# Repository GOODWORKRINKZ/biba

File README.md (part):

# BiBa

BiBa — это колесная робот-платформа с управлением по ExpressLRS/CRSF, телеметрией от Daly 6S BMS по BLE или USB-UART, двухканальными драйверами BTS7960 и звуковой индикацией через моторы. Платформа поддерживает три композиции железа — от чисто-Pi-варианта до связки одноплатник + STM32F103, поэтому репозиторий организован как hub: общие компоненты живут рядом, а сборки разводятся по подкаталогам.

## Архитектура

BiBa поддерживает три композиции железа. Где есть STM32 — именно он принимает CRSF и держит failsafe; одноплатник, если присутствует, работает как high-level brain поверх SPI-канала к STM32.

| Композиция | SBC (Raspberry Pi) | MCU add-on | Кто слушает CRSF | Compose / прошивка |
| --- | --- | --- | --- | --- |
| **A. Pi-only** (текущий продакшен) | да | нет | Pi (`/dev/ttyS0`) | [`docker/legacy-pi/docker-compose.yml`](docker/legacy-pi/docker-compose.yml) |
| **B. STM32-only** | нет | STM32F103 | STM32 | env `standalone` в [`firmware/`](firmware/) |
| **C. Pi + STM32** | да | STM32F103 | STM32 (Pi видит каналы через SPI-телеметрию) | env `companion` в [`firmware/`](firmware/) + ROS2-стек в `docker/ros2/` (в разработке) |
| **D. RP2040-only** (в разработке, ветка `rp2040-port`) | нет | RP2040 | RP2040 | env `rp2040_dc_bts7960_pwm_standalone` в [`firmware/`](firmware/) |

Канонический разбор композиций, их обязанности и failsafe-уровни — в [docs/system_architecture.md](docs/system_architecture.md). STM32-сторона детально описана в [docs/stm32_architecture.md](docs/stm32_architecture.md), будущий ROS2-стек композиции C — в [docs/ros2_stack.md](docs/ros2_stack.md). Общий design-doc и план редизайна — [docs/plans/2026-04-28-sbc-architecture-redesign-design.md](docs/plans/2026-04-28-sbc-architecture-redesign-design.md).

## Состав железа

- Raspberry Pi Zero 2W
- ELRS-приемник с подключением по UART/CRSF
- Daly BMS по BLE или с USB-UART адаптером
- 6S аккумулятор с телеметрией BMS
- Два драйвера BTS7960 для левого и правого моторов
- ADS1115 для current sense и телеметрии токов колёс (опционально)

## Распиновка

| Назначение | BCM | Физический пин |
| --- | --- | --- |
| ELRS TX | 14 | 8 |
| ELRS RX | 15 | 10 |
| I2C SDA (ADS1115, опционально) | 2 | 3 |
| I2C SCL (ADS1115, опционально) | 3 | 5 |
| Left BTS7960 RPWM | 12 | 32 |
| Left BTS7960 LPWM | 18 | 12 |
| Left BTS7960 REN | 23 | 16 |
| Left BTS7960 LEN | 24 | 18 |
| Right BTS7960 RPWM | 19 | 35 |
| Right BTS7960 LPWM | 13 | 33 |
| Right BTS7960 REN | 20 | 38 |
| Right BTS7960 LEN | 21 | 40 |
| GND драйвера | - | 14 |

Распиновка и таблица выше актуальны для композиции A (Pi-only). Для композиций B/C wiring между Pi, STM32 и силовой частью описан в [docs/wiring.md](docs/wiring.md) и [docs/stm32_architecture.md](docs/stm32_architecture.md).

Подробное описание подключения находится в [docs/wiring.md](docs/wiring.md).

Опциональная прошивка для STM32F103 ("Blue Pill") add-on, который умеет работать либо самостоятельно, либо SPI-slave-ом к Pi, живёт в [`firmware/`](firmware/). Архитектура описана в [docs/stm32_architecture.md](docs/stm32_architecture.md).

Текущий двухмоторный runtime на Pi Zero 2W должен быть запущен с `BTS7960_PWM_MODE=SOFTWARE`, потому что распиновка `12/18` и `19/13` делит общие hardware-PWM каналы. Это уже совпадает и с кодовым default в `config.py`, и с compose-default для развёрнутого робота.

## Структура репозитория

- `biba-controller/` — Python-контроллер для CRSF, моторов, моторного audio/voice runtime и телеметрии BMS (композиции A и C)
- `biba-controller/stm32_link/` — опциональный SPI-клиент к STM32F103 add-on (`STM32_LINK_ENABLED=1`, композиция C)
- `firmware/` — PlatformIO-проект прошивки (STM32F103C8T6 и RP2040): env'ы `standalone` для композиции B, `companion` для композиции C, `rp2040_dc_bts7960_pwm_standalone` для композиции D (ветка `rp2040-port`), `native_test` для host-side Unity-тестов
- `docker/` — каталог compose-стеков, разнесённых по композициям:
  - `docker/legacy-pi/` — текущий продакшен-стек композиции A
  - `docker/ros2/` — будущий ROS2-стек композиции C (в разработке)
  - `docker/base/` — общие базовые образы (в разработке)
- `lua/SCRIPTS/TELEMETRY/biba.lua` — экран телеметрии EdgeTX для оператора
- `.github/workflows/` — global builder workflows для Ruff, pytest, shellcheck и сборки arm64 Docker-образа в GHCR
- `scripts/setup/` — bringup-скрипты для Raspberry Pi (Docker, Compose, systemd-автозапуск)
- `scripts/biba_aliases.sh` — robot-side operational aliases, включая `bbupdate` для штатного обновления
- `scripts/diagnostics.sh` — диагностика хоста и контейнера
- `scripts/voice_prep.py` — офлайн-подготовка русскоязычных voice assets и явный promote в production voice каталог
- `voice-src/phrases.yml` — канонический набор русских фраз по событиям
- `voice-work/` — staging-каталог для сгенерированных кандидатов перед promote в production voice каталог
- `docs/deployment.md` — руководство по развёртыванию по композициям
- `docs/system_architecture.md` — канонический обзор всех трёх композиций
- `firmware/docs/openipc_wfb.md` — приём FPV-видео с OpenIPC-камеры по радио (RTL8812AU + wfb-ng)
- `.agents/skills/` — вендорный каталог skills

## Quick-start по композициям

- **Композиция A (Pi-only).** Сегодняшний bringup-скрипт и compose-стек. Полный гайд: [docs/deployment.md](docs/deployment.md#композиция-a-pi-only).
- **Композиция B (STM32-only).** Без одноплатника. Сборка и заливка прошивки описаны в [firmware/README.md](firmware/README.md) и [docs/stm32_architecture.md](docs/stm32_architecture.md).
- **Композиция C (Pi + STM32).** В разработке. Проектная картина — в [design-doc](docs/plans/2026-04-28-sbc-architecture-redesign-design.md) и [docs/ros2_stack.md](docs/ros2_stack.md).

Дальше по тексту разделы про подготовку Pi, env-переменные, settings UI и motor trim относятся к композиции A.

## Подготовка Raspberry Pi (композиция A)

1. Включите UART на Raspberry Pi.
2. Освободите основной UART от Bluetooth, добавив в конфигурацию:

   ```ini
   enable_uart=1
   dtoverlay=disable-bt
   ```

3. Перезагрузите Raspberry Pi.
4. Настройте Daly BMS по BLE или подключите USB-UART адаптер, если используете UART-вариант.
5. Если используете ADS1115 для current sense, включите I2C и проверьте наличие `/dev/i2c-1`.

Вместо ручной установки Docker/Compose можно использовать bringup-скрипт:

```bash
curl -fsSL https://raw.githubusercontent.com/GOODWORKRINKZ/biba/main/scripts/setup/setup_node.sh | bash
```

Скрипт:

- ставит Docker и Docker Compose plugin
- ставит базовые системные утилиты
- клонирует или обновляет репозиторий в `~/biba`
- настраивает алиасы для управления стеком
- создает `systemd` unit для автозапуска `docker compose`

## Запуск (композиция A)

Компоновка стека лежит в [`docker/legacy-pi/docker-compose.yml`](docker/legacy-pi/docker-compose.yml). На роботе все стандартные действия выполняются через `bb*`-aliases из [`scripts/biba_aliases.sh`](scripts/biba_aliases.sh) (`bbupdate`, `bbstart`, `bbstop`, `bblogs`, `bbpull`).

Если удобно работать без алиасов — указывайте compose-файл явно:

```bash
docker compose -f docker/legacy-pi/docker-compose.yml pull
docker compose -f docker/legacy-pi/docker-compose.yml up -d
```

Локальная сборка:

```bash
docker compose -f docker/legacy-pi/docker-compose.yml build
docker compose -f docker/legacy-pi/docker-compose.yml up -d
```

Путь к compose-файлу можно переопределить переменной `BIBA_COMPOSE_FILE` для скриптов и алиасов.

Контейнер запускает `pigpiod`, слушает ELRS CRSF кадры на `/dev/ttyS0`, управляет моторами, опрашивает Daly BMS по BLE или на `/dev/ttyUSB0` и отправляет батарейную телеметрию обратно на передатчик.

Docker-образ собирается под `linux/arm64`, чтобы совпадать с Raspberry Pi Zero 2W. Для этого `pigpiod` собирается внутри образа из upstream `pigpio`, так как готовый пакет `pigpio` отсутствует в Debian bookworm arm64.

## Конфигурация и переменные окружения (композиция A)

Все env-переменные ниже применяются к compose-стеку композиции A в [`docker/legacy-pi/docker-compose.yml`](docker/legacy-pi/docker-compose.yml). Тип драйвера и распиновку можно переопределить через них:

- `MOTOR_DRIVER_TYPE=BTS7960|PWM_DIR`
- `BTS7960_PWM_MODE=HARDWARE|SOFTWARE` — для Pi Zero 2W с текущей двухмоторной проводкой нужен `SOFTWARE`
- `PWM_FREQUENCY_HZ=20000` — частота software PWM; актуально только при `BTS7960_PWM_MODE=SOFTWARE`
- `LEFT_MOTOR_RPWM=12`
- `LEFT_MOTOR_LPWM=18`
- `LEFT_MOTOR_REN=23`
- `LEFT_MOTOR_LEN=24`
- `LEFT_MOTOR_ENABLED=1` — отключить левый мотор целиком (для отладки)
- `RIGHT_MOTOR_RPWM=19`
- `RIGHT_MOTOR_LPWM=13`
- `RIGHT_MOTOR_REN=20`
- `RIGHT_MOTOR_LEN=21`
- `RIGHT_MOTOR_ENABLED=1` — отключить правый мотор целиком (для отладки)
- `MOTOR1_INVERTED=0|1`
- `MOTOR2_INVERTED=0|1`
- `CRSF_BAUD=420000` — скорость UART для CRSF-приёмника (менять не нужно для стандартного ELRS)
- `ARM_THRESHOLD=0.3` — нормализованный порог CH_ARM для арминга
- `THROTTLE_FILTER_MODE=NONE|KALMAN` — фильтрация газа до wheel-mix; `NONE` по умолчанию, `KALMAN` сглаживает выбросы канала
- `THROTTLE_KALMAN_PROCESS_NOISE=0.02` — насколько быстро фильтр принимает изменения реального setpoint
- `THROTTLE_KALMAN_MEASUREMENT_NOISE=0.5` — насколько сильно фильтр подавляет шум и ложные выбросы канала
- `CH_SPEED_MODE=5` — `CH6` на передатчике; трёхпозиционный селектор скоростного режима для controller-side scaling газа и руля
- `CH_DRIVE_MODE=6` — `CH7` на передатчике; селектор режимов движения: `manual` и `stabilized`
- `DRIVE_MODE_LOW_THRESHOLD=-0.3`, `DRIVE_MODE_HIGH_THRESHOLD=0.3` — пороги переключения drive mode аналогично speed mode
- `SPEED_MODE_LOW_THRESHOLD=-0.3` — нижний порог селектора в нормализованном диапазоне `-1..1`; ниже этого значения включается режим `1`
- `SPEED_MODE_HIGH_THRESHOLD=0.3` — верхний порог селектора в нормализованном диапазоне `-1..1`; выше этого значения включается режим `3`
- `SPEED_MODE_SLOW_SCALE=0.3333333333333333` — коэффициент для режима `1`
- `SPEED_MODE_MEDIUM_SCALE=0.6666666666666666` — коэффициент для режима `2`
- `SPEED_MODE_FAST_SCALE=1.0` — коэффициент для режима `3`
- `IMU_ENABLED=0|1` — включает autodetect IMU backend на I2C: BMI160/BMI166 или ST LSM6DS3-class
- `IMU_I2C_BUS=1`, `IMU_I2C_ADDRESS=104`, `IMU_EXPECTED_CHIP_ID=209` — параметры подключения IMU; на текущем роботе ST-модуль отвечает по `0x6A`, так что для него нужен `IMU_I2C_ADDRESS=106`
- `IMU_SAMPLE_RATE_HZ=100.0`, `IMU_STALE_TIMEOUT_S=0.2`, `IMU_GYRO_BIAS_CALIBRATION_S=1.0`, `IMU_GYRO_Z_SIGN=1.0` — частота чтения, timeout свежести, длительность bias-калибровки и знак yaw-оси
- `DRIVE_MODE_STEERING_DEADBAND=0.05`, `DRIVE_MODE_STEERING_LIMIT=1.0`, `DRIVE_MODE_YAW_RATE_MAX_DPS=90.0` — базовые ограничения assist-контура
- `DRIVE_MODE_YAW_RATE_KP/KI/KD` — tuning-параметры yaw-rate контура stabilized режима
- `DRIVE_MODE_YAW_RATE_DEADBAND_DPS`, `DRIVE_MODE_YAW_RATE_FILTER_HZ` — подавление мелкого gyro noise и сглаживание yaw-rate feedback
- `DRIVE_MODE_STABILIZATION_MIN_THROTTLE`, `DRIVE_MODE_NEUTRAL_STABILIZATION_STEERING_LIMIT`, `DRIVE_MODE_NEUTRAL_STABILIZATION_MAX_THROTTLE` — low-speed ограничения stabilized режима
- `PID_TUNING_SETTINGS_PATH=/data/pid-tuning.json` — persistent JSON с последними field-tuning значениями stabilized режима
- `LOW_CELL_VOLTAGE=3.5` — порог низкого напряжения ячейки для предупреждения `LOW` на Lua-экране
- `LOW_PACK_VOLTAGE=21.0` — порог низкого напряжения пакета (резервный, если ячейки не доступны)
- `BMS_BLE_ADDRESS=` — MAC-адрес BLE BMS (пустая строка = авто-поиск)
- `BMS_BLE_TIMEOUT_S=1.5` — таймаут BLE-операций
- `BMS_BLE_SERVICE_UUID`, `BMS_BLE_WRITE_UUID`, `BMS_BLE_NOTIFY_UUID` — UUID BLE-сервиса Daly (менять не нужно для стандартного Daly)
- `BMS_TELEMETRY_TRACE_ENABLED=0|1` — включает точные controller-side trace-логи на этапах consume/send для battery telemetry
- `BEACON_ENABLED=1` — включён по умолчанию; `0` отключает маяк совсем
- `BEACON_DELAY_S=300`
- `CH_BEACON=7` — `CH8` на передатчике; ручное включение маяка
- `CH_MUTE=9` — `CH10` на передатчике по умолчанию; канал мьюта обычных звуков, если нужен отдельный mute switch
- `CH_TRIM=8` — `CH9` на передатчике; в trim-mode используется как live-источник подстройки межколёсного баланса
- `MOTOR_TRIM_MAX_EFFECT=0.30` — максимальная коррекция, применяемая к одной стороне от полного хода `CH9`
- `MOTOR_TRIM_CONFIRM_HOLD_S=5.0` — сколько секунд держать trim-жест для входа и подтверждения
- `MOTOR_TRIM_SETTINGS_PATH=/data/motor-trim.json` — файл сохранённого trim на persistent Docker volume
- `ENABLE_RC_MELODIES=0|1` — включает выбор BLHeli-мелодий с передатчика
- `CH_MELODY=8` — канал выбора мелодии, если `ENABLE_RC_MELODIES=1`
- `STARTUP_MELODY=biba_signature` — стартовая BLHeli-мелодия при включённом melody-runtime
- `SOUND_MODE=SPECTRAL_VOICE|VOICE|SYNTH` — режим звуковой индикации: `SPECTRAL_VOICE` (по умолчанию) использует build-time spectral cache, `VOICE` — raw WAV, `SYNTH` — только BLHeli-мелодии без голоса
- `VOICE_SELECTION_MODE=ROUND_ROBIN|RANDOM` — порядок воспроизведения WAV при наличии нескольких вариантов на событие
- `MOTOR_TEST_API_ENABLED=1` — включён по умолчанию; `0` отключает встроенный HTTP settings UI контроллера
- `MOTOR_TEST_API_HOST=0.0.0.0` — bind host для settings UI
- `MOTOR_TEST_API_PORT=8765` — bind port для settings UI
- `RAMP_ACCEL_RATE=2.0` — скорость разгона мотора (единиц/сек, 0→100% за 0.5с)
- `RAMP_DECEL_RATE=2.0` — скорость отпускания/торможения (единиц/сек, 100%→0 за 0.5с)
- `RAMP_REVERSE_DECEL_RATE=0.5` — скорость подхода к нулю перед сменой направления; меньше значение = мягче переход в реверс
- `RAMP_ZERO_HOLD_S=0.15` — пауза на нуле (секунды) после торможения перед реверсом; даёт мотору физически остановиться и убирает «гавканье» BTS7960
- `MOTOR_DEADBAND=0.05` — мёртвая зона стика (меньше порога → мотор стоит)

Если нужно включить current sense через ADS1115, дополнительно задайте:

- `MOTOR_CURRENT_SENSE_ENABLED=1`
- `MOTOR_CURRENT_LIMITING_ENABLED=0|1` — включает software throttle back при превышении тока
- `MOTOR_CURRENT_SENSE_I2C_ADDRESS=72` (0x48 — стандартный адрес ADS1115)
- `MOTOR_CURRENT_SENSE_SAMPLE_RATE_HZ=32.0` — частота опроса ADS1115
- `MOTOR_CURRENT_SENSE_GAIN=1` — коэффициент усиления ADS1115 (1, 2, 4, 8, 16)
- `LEFT_MOTOR_CURRENT_SENSE_FORWARD_CHANNEL=2`, `LEFT_MOTOR_CURRENT_SENSE_REVERSE_CHANNEL=3`
- `RIGHT_MOTOR_CURRENT_SENSE_FORWARD_CHANNEL=0`, `RIGHT_MOTOR_CURRENT_SENSE_REVERSE_CHANNEL=1`
- `LEFT_MOTOR_CURRENT_SENSE_ZERO_OFFSET_V=0.0`, `RIGHT_MOTOR_CURRENT_SENSE_ZERO_OFFSET_V=0.0` — нулевые смещения для калибровки
- `LEFT_MOTOR_CURRENT_SENSE_AMPS_PER_VOLT=1.0`, `RIGHT_MOTOR_CURRENT_SENSE_AMPS_PER_VOLT=1.0` — коэффициент перевода напряжения в амперы
- `LEFT_MOTOR_MAX_CURRENT_A=18.0`, `RIGHT_MOTOR_MAX_CURRENT_A=18.0` — пороги ограничения тока
- `LEFT_MOTOR_MAX_POWER_W=180.0`, `RIGHT_MOTOR_MAX_POWER_W=180.0` — пороги ограничения мощности
- `MOTOR_LIMIT_FALLBACK_VOLTAGE=24.0` — напряжение пакета для расчёта мощности при отсутствии BMS данных

Для калибровочных заездов доступен отдельный trace-режим current sense:

- `MOTOR_CURRENT_TRACE_ENABLED=0|1` — включает JSONL-лог с motor activity, ADS1115 и BMS snapshot
- `MOTOR_CURRENT_TRACE_PATH=/data/current-trace.jsonl` — путь к trace-файлу на persistent volume
- `MOTOR_CURRENT_TRACE_POST_ROLL_S=2.0` — сколько секунд держать запись после окончания motor activity
- `MOTOR_CURRENT_TRACE_MIN_INTERVAL_S=0.0` — минимальный интервал между sample-записями; `0.0` означает без дополнительного rate limit

Этот trace нужен для офлайн-калибровки токов колёс против более медленного тока BMS и по умолчанию выключен.

Опциональные параметры STM32 SPI companion link (композиция C, выключен по умолчанию):

- `STM32_LINK_ENABLED=0|1` — включает SPI-клиент к STM32F103 add-on
- `STM32_LINK_SPI_BUS=0`, `STM32_LINK_SPI_DEVICE=0` — номер шины и устройства SPI
- `STM32_LINK_SPI_SPEED_HZ=8000000` — скорость SPI

Прочие:

- `LOG_LEVEL=INFO` — уровень логирования контроллера (`DEBUG`, `INFO`, `WARNING`, `ERROR`)

## Settings UI

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
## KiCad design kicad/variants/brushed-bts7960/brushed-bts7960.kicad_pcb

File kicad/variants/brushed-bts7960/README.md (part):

# Вариант 1: коллекторные моторы + BTS7960 (`brushed-bts7960`)

Статус: **ревизия после разбора отказа U2**. Импорт из EasyEDA закрыт,
сверху внесена доработка по [analysis/M1-driver-failure.md](analysis/M1-driver-failure.md) §5:
керамика по питанию драйверов, DC-link, снабберы и супрессоры на выходах,
альтернативный DC/DC. Плата выросла до 180.5 × 100.3 мм. В схему добавлены
[антиспарк-выключатель и измерение тока/напряжения шины](#антиспарк-выключатель-2026-10-12)
(лист 2, `antispark.kicad_sch`) и интерфейс дочерней платы счётчика
пульсаций (лист 3, `ripple.kicad_sch`). ERC чистый. Плата пересобрана
2026-10-12: силовые клеммы J7–J9 на правом краю, одно место под DC/DC
(PM1, два набора отверстий), антиспарк у клеммы батареи; силовые цепи и
подключения DC/DC разведены, мелкая обвязка антиспарка и J6 — ещё нет
(см. [«Перенос на плату»](#перенос-на-плату-2026-10-12)).

## Что это

Первый (основной) вариант привода BiBa: два коллекторных редукторных мотора
**MY1016Z**, управляемые двумя модулями **BTS7960**, под управлением платы
**RP2040** (YD-RP2040 / RPi Pico-класс).

## Источник истины

- Таргет: `firmware/targets/RP2040_DC_BTS7960_PWM/` — `target.md` (распиновка), `target.h` (пины).
- Варианты: `docs/variants.md`.
- Шасси: `firmware/tools/cad/sbiba_chassis.py` — MY1016Z 24 В / 250 Вт,
  колесо насаживается прямо на выходной вал редуктора.

## Gerber-анализ (архив 2026-05-27)

Исходник: `Gerber_RP2040_PCB_RP2040_2026-05-27.zip` — экспорт из **EasyEDA**
(`How-to-order-PCB.txt` ссылается на docs.easyeda.com). Двухслойная плата,
нетлиста (IPC-356) в архиве **нет** → схема из гербера напрямую не
восстанавливается (в герберах только разводка и шелкография, без номиналов
и соединений на уровне схемы).

Отрендеренные слои: `gerber/render/` (рендер — `scripts/gerber_render.py`,
через pygerber). Состав платы по меди + шелкографии:

- Слева: посадочное место **RP2040-модуля** (два ряда площадок) + разъём `MPU` (J7).
- Центр: аналоговая обвязка **U1 + RC** (R4–R24, C1–C12) — RC-фильтры и делители.
- Справа: два силовых блока **BTS7960** (M1, M2), толстые токовые дорожки.
- Разъёмы: `UART1` (RX/TX/+5V/SW), `CRSF` (+/−/TX/RX), `BAT`, площадка приёмника `2.4 GHz`.
- Низ: GND-полигон + сигнальная разводка, сквозные переходные.

## Восстановленная схема (из EasyEDA-исходника)

Исходник EasyEDA лежит в `easyeda/RP2040/` (`RP2040.json` — схема,
`PCB_RP2040.json` — плата). Из него восстановлены **57 компонентов и 56 сетей**:

- `easyeda/RP2040/netlist.txt` — полный нетлист (сеть → пины).
- `easyeda/RP2040/components.tsv` — список компонентов (обозначение, номинал, корпус, LCSC).
- Парсер: `scripts/easyeda_netlist.py`.

Архитектура (точнее, чем в `target.md`):

- **Питание:** VIN (24 В) → C9 1000 мкФ → **PM1 SKMW30G-05** (24→5 В) → +5V;
  +5V → **U7 SPX3819M5-L-3-3** (5→3.3 В) → 3.3V.
- **MCU:** IC1 — RP2040 breakout (44 пина), распиновка совпадает с `target.h`.
- **Драйверы моторов:** **4× BTN7970** (U2–U5), по два полумоста на мотор
  (левый: U2 high + U3 low; правый: U4 high + U5 low). Выходы M1+/M1− и M2+/M2−.
- **Буфер:** U1 **SN74AHC244DW** — 8 линий PWM/EN от RP2040 → IN/INH драйверов.
- **IMU:** U6 **BMI160** на I2C0 (GP20/GP21) + INT на GP22, подтяжки R22/R23 10 кОм.
- **Токовый сенс:** IS драйверов → R17–R20 (1 кОм) → R_IS/L_IS → RC (C2/C3 0.1 мкФ)
  → IC1.31/32; R11–R16 (10 кОм) — подтяжки IS к GND.
- **VBAT/IBAT:** R26/R25 (1 кОм) → IC1.34/35; разъём H10 (GND/VBAT/IBAT).
- **Периферия:** J3 CRSF (+5V/GND/TX/RX), J4 UART1 (+5V/GND/TX/RX);
  свободные GP10–GP19 выведены на H1–H8 (1×3: GPIO, +5V, GND).
- **Включение:** единственный выключатель питания — **J5** на листе 2
  (антиспарк). J2 (SW/GND/+5V/GND) раньше управлял DC/DC через R.C./CTRL;
  с 2026-10-12 его вывод SW не подключён, вместо него на цепи `SW` стоит
  сервисная паяльная перемычка **JP3** (открыта = DC/DC включён). J1 (+5V/PM1_4/GND).

## Состав (блок-схема)

```mermaid
flowchart LR
    BAT["Батарея 24 В<br/>(Daly BMS)"] --> AS["Антиспарк<br/>LTC7004 + 2× N-MOSFET<br/>выключатель J5"]
    AS --> VIN["Шина VIN"]
    VIN --> VBAT["Делитель VBAT<br/>GP28 (ADC2)"]
    VIN --> IBAT["Датчик тока батареи<br/>GP29 (ADC3)"]
    VIN --> DCDC["DC/DC 24→5 В<br/>(панели, плата)"]
    VIN --> BTS_L["BTS7960 (левый)"]
    VIN --> BTS_R["BTS7960 (правый)"]
    RP["Плата RP2040"] -- "RPWM/LPWM + REN/LEN" --> BTS_L
    RP -- "RPWM/LPWM + REN/LEN" --> BTS_R
    BTS_L -- "IS (RC-фильтр)" --> RP
    BTS_R -- "IS (RC-фильтр)" --> RP
    BTS_L --> M_L["MY1016Z 24 В / 250 Вт (левый)"]
    BTS_R --> M_R["MY1016Z 24 В / 250 Вт (правый)"]
    CRSF["Приёмник CRSF/ELRS"] <-->|"UART0 (GP0/GP1)"| RP
    IMU["IMU BMI160 / LSM6DS3"] <-->|"I2C0 (GP20/GP21) + INT (GP22)"| RP
    SBC["Одноплатник"] <-->|"UART1 (GP12/GP13)"| RP
    RP --> RGB["RGB WS2812 (GP23, onboard)"]
    RP --> PANEL["LED-панели 2×4×4 (GP14)"]
```

## Распиновка RP2040 (из `target.h`)

| GP  | Функция | Сигнал | Направление | Примечание |
|-----|---------|--------|-------------|------------|
| GP0 | UART0_TX | CRSF TX | ВЫХ | к RX приёмника |
| GP1 | UART0_RX | CRSF RX | ВХ | от TX приёмника |
| GP2 | PWM1A | L_RPWM | ВЫХ ШИМ | слайс 1, канал A |
| GP3 | PWM1B | L_LPWM | ВЫХ ШИМ | слайс 1, канал B |
| GP4 | GPIO OUT | L_REN | ВЫХ | enable правого полумоста (левый драйвер) |
| GP5 | GPIO OUT | L_LEN | ВЫХ | enable левого полумоста (левый драйвер) |
| GP6 | PWM3A | R_RPWM | ВЫХ ШИМ | слайс 3, канал A |
| GP7 | PWM3B | R_LPWM | ВЫХ ШИМ | слайс 3, канал B |
| GP8 | GPIO OUT | R_REN | ВЫХ | enable правого полумоста (правый драйвер) |
| GP9 | GPIO OUT | R_LEN | ВЫХ | enable левого полумоста (правый драйвер) |
| GP10–GP11 | — | PULSE_L / PULSE_R | ВХ | зарезервированы под дочернюю плату счётчика пульсаций (J6, лист 3) |
| GP12 | UART1_TX | SBC TX | ВЫХ | RP2040 → одноплатник |
| GP13 | UART1_RX | SBC RX | ВХ | одноплатник → RP2040 |
| GP14 | PIO OUT | LED_PANEL | ВЫХ | цепочка WS2812: GP14 → левая → правая |
| GP15 | — | free | — | свободен |
| GP16–GP19 | — | free | — | свободны (SPI0/I2C1/UART0 по выбору) |
| GP20 | I2C0_SDA | IMU SDA | I/O | |
| GP21 | I2C0_SCL | IMU SCL | ВЫХ | |
| GP22 | GPIO IN | IMU INT1 | ВХ | прерывание IMU |
| GP23 | WS2812 | RGB_LED | ВЫХ | NeoPixel на YD-RP2040 |
| GP25 | GPIO OUT | STATUS_LED | ВЫХ | встроенный LED Pico, активный HIGH |
| GP26 | ADC0 | IS_RIGHT | ВХ | RC-фильтр 1 кΩ‖1 кΩ + 0.1 µF от IS правого BTS7960 |
| GP27 | ADC1 | IS_LEFT | ВХ | RC-фильтр 1 кΩ‖1 кΩ + 0.1 µF от IS левого BTS7960 |
| GP28 | ADC2 | VBAT | ВХ | делитель напряжения, коэфф. `BIBA_VBAT_DIVIDER_RATIO` |
| GP29 | ADC3 | IBAT | ВХ | выход датчика тока батареи |

## Силовые цепи

- Клемма **BAT+** — батарея (Daly BMS) → антиспарк-выключатель (лист 2) →
  шина **VIN**.
- Шина **VIN (24 В)** — оба BTS7960, датчик тока батареи, вход DC/DC 24→5 В.
  На плате до переноса антиспарка клемма батареи и есть VIN.
- Шина **5 В** — питание LED-панелей и Vin платы RP2040
  (панели в худшем случае ~0.9 А на 32 светодиода, белый на ходу).
- Шина **3.3V** — с LDO U7 (SPX3819, 5→3.3 В); питает U1, IMU, INA240, J6.
  Выводы 3V3 платы RP2040 (IC1.36/41) не подключены — у модуля свой стабилизатор.
- Общая земля силовой и логической частей (как в `docs/wiring.md`).
- Клеммы — площадки под пайку провода 5×4 мм (Ø2 мм, шаг 7.62) на правом
  краю платы: **J7** M1 (+/−), **J8** M2, **J9** BAT (+ / GND); плюс всегда
  верхняя площадка.

## Измерения (АЦП)

| Канал | Пин | Сигнал | Калибровка |
|-------|-----|--------|------------|
| ADC0 | GP26 | IS_RIGHT | RC 1 кΩ‖1 кΩ + 0.1 µF от IS-пинов BTS7960 |
| ADC1 | GP27 | IS_LEFT | RC 1 кΩ‖1 кΩ + 0.1 µF от IS-пинов BTS7960 |
| ADC2 | GP28 | VBAT | `BIBA_VBAT_DIVIDER_RATIO = 10.12` (калибровано 2026-05-26) |
| ADC3 | GP29 | IBAT | `BIBA_IBAT_AMPS_PER_VOLT = 1.0`, `BIBA_IBAT_ZERO_OFFSET_V = 0.0` |

Ключевые константы из `firmware/include/biba_config.h`:

- `BIBA_PWM_FREQUENCY_HZ = 20000` (несущая 20 кГц, выше слышимого).
- `BIBA_CONTROL_LOOP_HZ = 500`, `BIBA_TELEMETRY_PUBLISH_HZ = 200`.
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
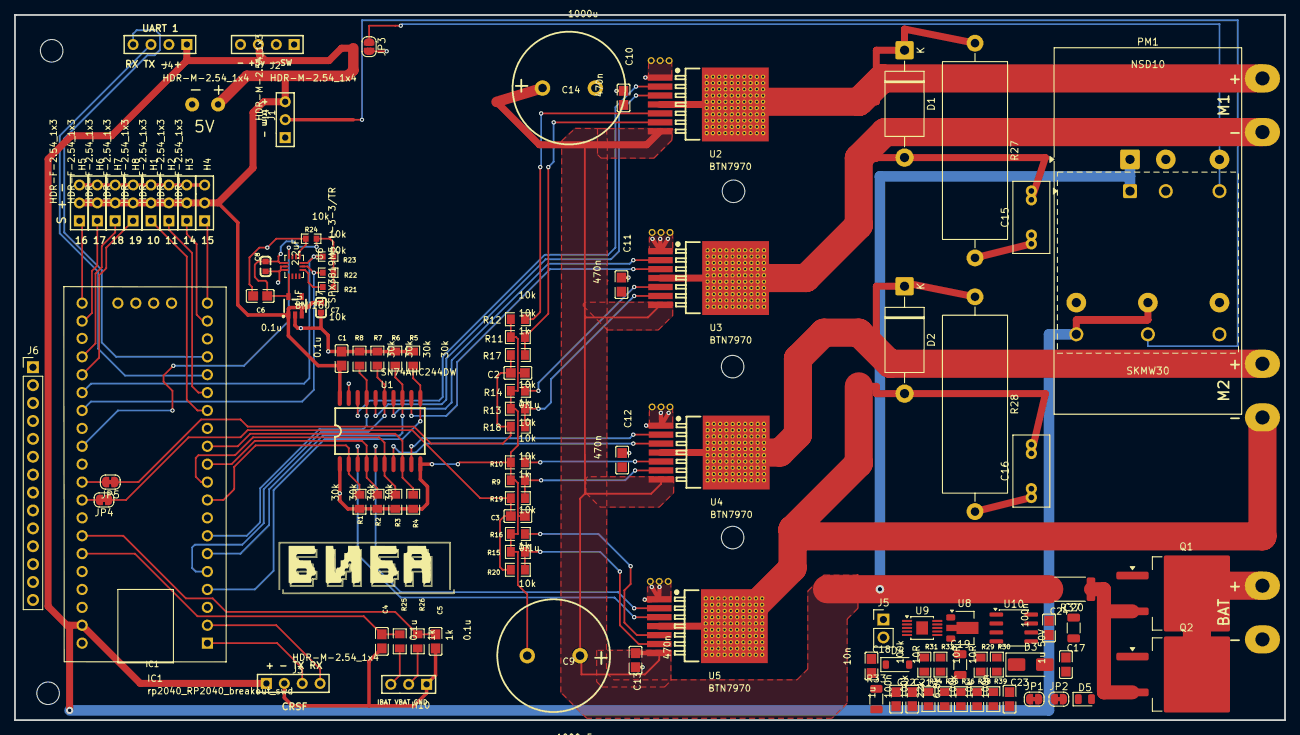
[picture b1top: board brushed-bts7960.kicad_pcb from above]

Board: 2 copper layers, 180.3 x 100.1 mm, 524 parts (0 on the bottom side), 75 nets.

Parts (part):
C1, C2, C3, C4, C5, C6: 0.1u; C0805
C7: 1uF; C0603
C8: 2.2uF; C0603
C9: 1000uF; CAP-TH_BD16.0-P7.50-D0.8-FD-H25.0
C10, C11, C12, C13: 470n; C0805
C14: 1000u; CAP-TH_BD16.0-P7.50-D0.8-FD-H25.0
C15, C16: 100n 100V; C_Rect_L10.0mm_W5.0mm_P5.00mm_P7.50mm
C17: 1u 50V; C0805
C18: 10n; C0805
C19: 470n 100V; C_1206_3216Metric
C20: 10u 25V; C_1206_3216Metric
C21, C23, C24: 100n; C0805
C22: 1u; C0805
D1, D2: 1.5KE30CA; D_DO-201AE_P15.24mm_Horizontal
D3: 27V; D_SMA
D4: BAS116; D_SOD-123
D5: LED зел.; LED_0805_2012Metric
H1, H2, H3, H4, H5, H6, H7, H8, H10: HDR-F-2.54_1x3; HDR-F-2.54_1X3
Hole_gge31981: Hole_gge31981
Hole_gge31996: Hole_gge31996
Hole_gge32011: Hole_gge32011
Hole_gge53711: Hole_gge53711
Hole_gge53741: Hole_gge53741
IC1: rp2040_RP2040_breakout_swd; RP2040-BREAKOUT_SWD
J1: HDR-M-2.54_1x3; HDR-M-2.54_1X3
J2, J3, J4: HDR-M-2.54_1x4; HDR-M-2.54_1X4
J5: SW_ON; PinHeader_1x02_P2.54mm_Vertical
J6: RIPPLE; PinHeader_1x14_P2.54mm_Vertical
J7: M1; WirePad_1x2_P7.62mm_D2.0mm
J8: M2; WirePad_1x2_P7.62mm_D2.0mm
J9: BAT; WirePad_1x2_P7.62mm_D2.0mm
JP1: VBAT c платы; SolderJumper-2_P1.3mm_Bridged_RoundedPad1.0x1.5mm
JP2: IBAT c платы; SolderJumper-2_P1.3mm_Bridged_RoundedPad1.0x1.5mm
JP3: DC/DC OFF (сервис); SolderJumper-2_P1.3mm_Open_RoundedPad1.0x1.5mm
JP4: IS_L→ADC; SolderJumper-2_P1.3mm_Bridged_RoundedPad1.0x1.5mm
JP5: IS_R→ADC; SolderJumper-2_P1.3mm_Bridged_RoundedPad1.0x1.5mm
PM1: SKMW30G-05 / NSD10-12S5; DCDC_SKMW30_NSD10
Pad_gge32188: Pad_gge32188
Pad_gge32224: Pad_gge32224
Pad_gge32248: Pad_gge32248
Pad_gge32347: Pad_gge32347
Pad_gge32350: Pad_gge32350
Pad_gge32353: Pad_gge32353
Pad_gge32416: Pad_gge32416
Pad_gge32419: Pad_gge32419
Pad_gge32422: Pad_gge32422
Pad_gge32482: Pad_gge32482
Pad_gge32485: Pad_gge32485
Pad_gge32488: Pad_gge32488
Pad_gge61193: Pad_gge61193
Pad_gge61325: Pad_gge61325
Pad_gge61349: Pad_gge61349
Pad_gge61511: Pad_gge61511
Pad_gge61535: Pad_gge61535
Pad_gge61559: Pad_gge61559
Pad_gge61583: Pad_gge61583
Pad_gge61607: Pad_gge61607
Pad_gge61754: Pad_gge61754
Pad_gge61757: Pad_gge61757
Pad_gge61760: Pad_gge61760
Pad_gge61763: Pad_gge61763
Pad_gge61766: Pad_gge61766
Pad_gge61769: Pad_gge61769
Pad_gge61772: Pad_gge61772
Pad_gge61775: Pad_gge61775
Pad_gge61898: Pad_gge61898
Pad_gge61901: Pad_gge61901
Pad_gge61904: Pad_gge61904
Pad_gge61907: Pad_gge61907
Pad_gge61910: Pad_gge61910
Pad_gge61913: Pad_gge61913
Pad_gge61916: Pad_gge61916
Pad_gge61919: Pad_gge61919
Pad_gge62042: Pad_gge62042
Pad_gge62045: Pad_gge62045
Pad_gge62048: Pad_gge62048
Pad_gge62051: Pad_gge62051
Pad_gge62054: Pad_gge62054
Pad_gge62057: Pad_gge62057
Pad_gge62060: Pad_gge62060
Pad_gge62063: Pad_gge62063
Pad_gge62186: Pad_gge62186
Pad_gge62189: Pad_gge62189
Pad_gge62192: Pad_gge62192
Pad_gge62195: Pad_gge62195
Pad_gge62198: Pad_gge62198
Pad_gge62201: Pad_gge62201
Pad_gge62204: Pad_gge62204
Pad_gge62207: Pad_gge62207
Pad_gge62330: Pad_gge62330
Pad_gge62333: Pad_gge62333
Pad_gge62336: Pad_gge62336
Pad_gge62339: Pad_gge62339
Pad_gge62342: Pad_gge62342
Pad_gge62345: Pad_gge62345
Pad_gge62348: Pad_gge62348
Pad_gge62351: Pad_gge62351
Pad_gge62474: Pad_gge62474
Pad_gge62477: Pad_gge62477
Pad_gge62480: Pad_gge62480
Pad_gge62483: Pad_gge62483
Pad_gge62486: Pad_gge62486
Pad_gge62489: Pad_gge62489
Pad_gge62492: Pad_gge62492
Pad_gge62495: Pad_gge62495
Pad_gge62618: Pad_gge62618
Pad_gge62621: Pad_gge62621
Pad_gge62624: Pad_gge62624
Pad_gge62627: Pad_gge62627
Pad_gge62630: Pad_gge62630
Pad_gge62633: Pad_gge62633
Pad_gge62636: Pad_gge62636
Pad_gge62639: Pad_gge62639
Pad_gge63914: Pad_gge63914
Pad_gge63917: Pad_gge63917
Pad_gge63920: Pad_gge63920
Pad_gge63923: Pad_gge63923
Pad_gge63926: Pad_gge63926
Pad_gge63929: Pad_gge63929
Pad_gge63932: Pad_gge63932
Pad_gge63935: Pad_gge63935
Pad_gge64058: Pad_gge64058
Pad_gge64061: Pad_gge64061
Pad_gge64064: Pad_gge64064
Pad_gge64067: Pad_gge64067
Pad_gge64070: Pad_gge64070
Pad_gge64073: Pad_gge64073
Pad_gge64076: Pad_gge64076
Pad_gge64079: Pad_gge64079
Pad_gge64232: Pad_gge64232
Pad_gge64235: Pad_gge64235
Pad_gge64238: Pad_gge64238
Pad_gge64241: Pad_gge64241
Pad_gge64244: Pad_gge64244
Pad_gge64247: Pad_gge64247
Pad_gge64250: Pad_gge64250
Pad_gge64253: Pad_gge64253
Pad_gge64256: Pad_gge64256
Pad_gge64259: Pad_gge64259
Pad_gge64592: Pad_gge64592
Pad_gge64595: Pad_gge64595
Pad_gge64598: Pad_gge64598
Pad_gge64601: Pad_gge64601
Pad_gge64604: Pad_gge64604
Pad_gge64607: Pad_gge64607
Pad_gge64610: Pad_gge64610
Pad_gge64613: Pad_gge64613
Pad_gge64616: Pad_gge64616
Pad_gge64619: Pad_gge64619
Pad_gge66122: Pad_gge66122
Pad_gge66125: Pad_gge66125
Pad_gge66128: Pad_gge66128
Pad_gge66131: Pad_gge66131
Pad_gge66134: Pad_gge66134
Pad_gge66137: Pad_gge66137
Pad_gge66140: Pad_gge66140
Pad_gge66143: Pad_gge66143
Pad_gge66146: Pad_gge66146
Pad_gge66149: Pad_gge66149
Pad_gge66152: Pad_gge66152
Pad_gge66155: Pad_gge66155
Pad_gge66158: Pad_gge66158
Pad_gge66161: Pad_gge66161
Pad_gge66164: Pad_gge66164
Pad_gge66167: Pad_gge66167
Pad_gge66170: Pad_gge66170
Pad_gge66173: Pad_gge66173
Pad_gge66176: Pad_gge66176
Pad_gge66179: Pad_gge66179
Pad_gge66182: Pad_gge66182
Pad_gge66185: Pad_gge66185
Pad_gge66188: Pad_gge66188
Pad_gge66191: Pad_gge66191
Pad_gge66194: Pad_gge66194
Pad_gge66197: Pad_gge66197
Pad_gge66200: Pad_gge66200
Pad_gge66203: Pad_gge66203
Pad_gge66206: Pad_gge66206
Pad_gge66209: Pad_gge66209
Pad_gge66212: Pad_gge66212
Pad_gge66215: Pad_gge66215
Pad_gge66218: Pad_gge66218
Pad_gge66221: Pad_gge66221
Pad_gge66224: Pad_gge66224
Pad_gge66227: Pad_gge66227
Pad_gge66230: Pad_gge66230
Pad_gge66233: Pad_gge66233
Pad_gge66236: Pad_gge66236
Pad_gge66239: Pad_gge66239
Pad_gge66242: Pad_gge66242
Pad_gge66245: Pad_gge66245
Pad_gge66248: Pad_gge66248
Pad_gge66251: Pad_gge66251
Pad_gge66254: Pad_gge66254
Pad_gge66257: Pad_gge66257
Pad_gge66260: Pad_gge66260
Pad_gge66263: Pad_gge66263
Pad_gge66266: Pad_gge66266
Pad_gge66269: Pad_gge66269
Pad_gge66272: Pad_gge66272
Pad_gge66275: Pad_gge66275
Pad_gge66278: Pad_gge66278
Pad_gge66281: Pad_gge66281
Pad_gge66284: Pad_gge66284
Pad_gge66287: Pad_gge66287
Pad_gge66290: Pad_gge66290
Pad_gge66293: Pad_gge66293
Pad_gge66296: Pad_gge66296
Pad_gge66299: Pad_gge66299
Pad_gge66302: Pad_gge66302
Pad_gge66305: Pad_gge66305
Pad_gge66308: Pad_gge66308
Pad_gge66311: Pad_gge66311
Pad_gge66314: Pad_gge66314
Pad_gge66317: Pad_gge66317
Pad_gge66320: Pad_gge66320
Pad_gge66323: Pad_gge66323
Pad_gge66326: Pad_gge66326
Pad_gge66329: Pad_gge66329
Pad_gge66332: Pad_gge66332
Pad_gge66335: Pad_gge66335
Pad_gge66338: Pad_gge66338
Pad_gge66341: Pad_gge66341
Pad_gge66344: Pad_gge66344
Pad_gge66347: Pad_gge66347
Pad_gge66350: Pad_gge66350
Pad_gge66353: Pad_gge66353
Pad_gge66356: Pad_gge66356
Pad_gge66359: Pad_gge66359
Pad_gge66362: Pad_gge66362
Pad_gge66365: Pad_gge66365
Pad_gge66368: Pad_gge66368
Pad_gge66371: Pad_gge66371
Pad_gge66374: Pad_gge66374
Pad_gge66377: Pad_gge66377
Pad_gge66380: Pad_gge66380
Pad_gge66383: Pad_gge66383
Pad_gge66386: Pad_gge66386
Pad_gge66389: Pad_gge66389
Pad_gge66392: Pad_gge66392
Pad_gge66395: Pad_gge66395
Pad_gge66398: Pad_gge66398
Pad_gge66401: Pad_gge66401
Pad_gge66404: Pad_gge66404
Pad_gge66407: Pad_gge66407
Pad_gge66410: Pad_gge66410
Pad_gge66413: Pad_gge66413
Pad_gge66416: Pad_gge66416
Pad_gge66419: Pad_gge66419
Pad_gge67922: Pad_gge67922
Pad_gge67925: Pad_gge67925
Pad_gge67928: Pad_gge67928
Pad_gge67931: Pad_gge67931
Pad_gge67934: Pad_gge67934
Pad_gge67937: Pad_gge67937
Pad_gge67940: Pad_gge67940
Pad_gge67943: Pad_gge67943
Pad_gge67946: Pad_gge67946
Pad_gge67949: Pad_gge67949
Pad_gge67952: Pad_gge67952
Pad_gge67955: Pad_gge67955
Pad_gge67958: Pad_gge67958
Pad_gge67961: Pad_gge67961
Pad_gge67964: Pad_gge67964
Pad_gge67967: Pad_gge67967
Pad_gge67970: Pad_gge67970
Pad_gge67973: Pad_gge67973
Pad_gge67976: Pad_gge67976
Pad_gge67979: Pad_gge67979
Pad_gge67982: Pad_gge67982
Pad_gge67985: Pad_gge67985
Pad_gge67988: Pad_gge67988
Pad_gge67991: Pad_gge67991
Pad_gge67994: Pad_gge67994
Pad_gge67997: Pad_gge67997
Pad_gge68000: Pad_gge68000
Pad_gge68003: Pad_gge68003
Pad_gge68006: Pad_gge68006
Pad_gge68009: Pad_gge68009
Pad_gge68012: Pad_gge68012
Pad_gge68015: Pad_gge68015
Pad_gge68018: Pad_gge68018
Pad_gge68021: Pad_gge68021
Pad_gge68024: Pad_gge68024
Pad_gge68027: Pad_gge68027
Pad_gge68030: Pad_gge68030
Pad_gge68033: Pad_gge68033
Pad_gge68036: Pad_gge68036
Pad_gge68039: Pad_gge68039
Pad_gge68042: Pad_gge68042
Pad_gge68045: Pad_gge68045
Pad_gge68048: Pad_gge68048
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
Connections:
3.3V: C6.1, C8.1, C24.2, J6.2, R21.1, R22.2, R23.2, R24.2, U6.5, U6.8, U7.5, U10.6, U10.7
+5V: C1.1, C7.2, H1.2, H2.2, H3.2, H4.2, H5.2, H6.2, H7.2, H8.2, IC1.39, J1.3, J2.3, J3.1, J4.1, J6.3, PM1.3, Pad_gge70032.27, U1.20, U7.1, U7.3
/M1_SNUB: C15.1, R27.2
/M2_SNUB: C16.1, R28.2
/Антиспарк (LTC7004)/G_SW: R29.1, R30.2, R31.2, R32.1, U9.6
/Антиспарк (LTC7004)/SW_IN: J5.2, R33.1, R34.1
/Антиспарк (LTC7004)/VCC_AS: C21.1, C22.1, D4.2, U8.1, U9.1
ADC_L: IC1.32, J6.6, JP4.2
ADC_R: IC1.31, J6.7, JP5.2
BAT+: J5.1, J9.1, Q1.2, Q2.2
CRSF_RX: IC1.2, J3.4
CRSF_TX: IC1.1, J3.3
GND: C1.2, C2.1, C3.1, C4.2, C5.2, C6.2, C7.1, C8.2, C9.2, C10.2, C11.2, C12.2, C13.2, C14.2, C17.2, C18.2, C21.2, C22.2, C23.1, C24.1, D3.2, D5.1, H1.3, H2.3, H3.3, H4.3, H5.3, H6.3, H7.3, H8.3, H10.1, IC1.3, IC1.8, IC1.13, IC1.18, IC1.23, IC1.28, IC1.33, IC1.38, IC1.44, J1.1, J2.2, J2.4, J3.2, J4.2, J6.1, J6.14, J9.2, JP3.2, PM1.2, PM1.5, Pad_gge32188.7, Pad_gge32224.8, Pad_gge32248.9, Pad_gge32347.7, Pad_gge32350.8, Pad_gge32353.9, Pad_gge32416.7, Pad_gge32419.8, Pad_gge32422.9, Pad_gge32482.7, Pad_gge32485.8, Pad_gge32488.9, Pad_gge70234.28, R1.1, R2.1, R3.1, R4.1, R5.1, R6.1, R7.1, R8.1, R9.1, R10.1, R11.1, R12.1, R13.1, R14.2, R15.2, R16.1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
GP10: H1.1, IC1.14, J6.8
GP11: H2.1, IC1.15, J6.9
GP14: H3.1, IC1.19
GP15: H4.1, IC1.20
GP16: H5.1, IC1.21, J6.12
GP17: H6.1, IC1.22, J6.13
GP18: H7.1, IC1.24, J6.10
GP19: H8.1, IC1.25, J6.11
I2C0_SCL: IC1.27, R22.1, U6.13
I2C0_SDA: IC1.26, R23.1, U6.14
IBAT: H10.3, JP2.2, R25.2
IMU_INT1: IC1.29, U6.4
IN1: U1.18, U2.2
IN2: U1.14, U3.2
IN3: U1.9, U4.2
IN4: U1.5, U5.2
INH1: U1.16, U2.3
INH2: U1.12, U3.3
INH3: U1.7, U4.3
INH4: U1.3, U5.3
L_IS: C3.2, J6.4, JP4.1, R19.1, R20.1
L_LEN: IC1.7, R8.2, U1.17
L_LPWM: IC1.5, R7.2, U1.15
L_REN: IC1.6, R6.2, U1.13
L_RPWM: IC1.4, R5.2, U1.11
M1+: D1.1, J7.1, Pad_gge61193.10, Pad_gge61325.15, Pad_gge61349.16, Pad_gge61511.22, Pad_gge61535.23, Pad_gge61559.24, Pad_gge61583.25, Pad_gge61607.26, Pad_gge61754.26, Pad_gge61757.25, Pad_gge61760.24, Pad_gge61763.23, Pad_gge61766.22, Pad_gge61769.16, Pad_gge61772.15, Pad_gge61775.10, Pad_gge61898.26, Pad_gge61901.25, Pad_gge61904.24, Pad_gge61907.23, Pad_gge61910.22, Pad_gge61913.16, Pad_gge61916.15, Pad_gge61919.10, Pad_gge62042.26, Pad_gge62045.25, Pad_gge62048.24, Pad_gge62051.23, Pad_gge62054.22, Pad_gge62057.16, Pad_gge62060.15, Pad_gge62063.10, Pad_gge62186.26, Pad_gge62189.25, Pad_gge62192.24, Pad_gge62195.23, Pad_gge62198.22, Pad_gge62201.16, Pad_gge62204.15, Pad_gge62207.10, Pad_gge62330.26, Pad_gge62333.25, Pad_gge62336.24, Pad_gge62339.23, Pad_gge62342.22, Pad_gge62345.16, Pad_gge62348.15, Pad_gge62351.10, Pad_gge62474.26, Pad_gge62477.25, Pad_gge62480.24, Pad_gge62483.23, Pad_gge62486.22, Pad_gge62489.16, Pad_gge62492.15, Pad_gge62495.10, Pad_gge62618.26, Pad_gge62621.25, Pad_gge62624.24, Pad_gge62627.23, Pad_gge62630.22, Pad_gge62633.16, Pad_gge62636.15, Pad_gge62639.10, Pad_gge63914.26, Pad_gge63917.26, Pad_gge63920.26, Pad_gge63923.26, Pad_gge63926.26, Pad_gge63929.26, Pad_gge63932.26, Pad_gge63935.26, Pad_gge64058.26, Pad_gge64061.26, Pad_gge64064.26, Pad_gge64067.26, Pad_gge64070.26, Pad_gge64073.26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
M1-: C15.2, D1.2, J7.2, Pad_gge66122.26, Pad_gge66125.25, Pad_gge66128.24, Pad_gge66131.23, Pad_gge66134.22, Pad_gge66137.16, Pad_gge66140.15, Pad_gge66143.10, Pad_gge66146.26, Pad_gge66149.26, Pad_gge66152.26, Pad_gge66155.25, Pad_gge66158.24, Pad_gge66161.23, Pad_gge66164.22, Pad_gge66167.16, Pad_gge66170.15, Pad_gge66173.10, Pad_gge66176.26, Pad_gge66179.26, Pad_gge66182.26, Pad_gge66185.26, Pad_gge66188.26, Pad_gge66191.26, Pad_gge66194.26, Pad_gge66197.26, Pad_gge66200.26, Pad_gge66203.26, Pad_gge66206.26, Pad_gge66209.26, Pad_gge66212.26, Pad_gge66215.26, Pad_gge66218.26, Pad_gge66221.26, Pad_gge66224.26, Pad_gge66227.26, Pad_gge66230.10, Pad_gge66233.15, Pad_gge66236.16, Pad_gge66239.22, Pad_gge66242.23, Pad_gge66245.24, Pad_gge66248.25, Pad_gge66251.26, Pad_gge66254.10, Pad_gge66257.15, Pad_gge66260.16, Pad_gge66263.22, Pad_gge66266.23, Pad_gge66269.24, Pad_gge66272.25, Pad_gge66275.26, Pad_gge66278.10, Pad_gge66281.15, Pad_gge66284.16, Pad_gge66287.22, Pad_gge66290.23, Pad_gge66293.24, Pad_gge66296.25, Pad_gge66299.26, Pad_gge66302.10, Pad_gge66305.15, Pad_gge66308.16, Pad_gge66311.22, Pad_gge66314.23, Pad_gge66317.24, Pad_gge66320.25, Pad_gge66323.26, Pad_gge66326.10, Pad_gge66329.15, Pad_gge66332.16, Pad_gge66335.22, Pad_gge66338.23, Pad_gge66341.24, Pad_gge66344.25, Pad_gge66347.26, Pad_gge66350.10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
M2+: D2.1, J8.1, Pad_gge67922.26, Pad_gge67925.25, Pad_gge67928.24, Pad_gge67931.23, Pad_gge67934.22, Pad_gge67937.16, Pad_gge67940.15, Pad_gge67943.10, Pad_gge67946.26, Pad_gge67949.26, Pad_gge67952.26, Pad_gge67955.25, Pad_gge67958.24, Pad_gge67961.23, Pad_gge67964.22, Pad_gge67967.16, Pad_gge67970.15, Pad_gge67973.10, Pad_gge67976.26, Pad_gge67979.26, Pad_gge67982.26, Pad_gge67985.26, Pad_gge67988.26, Pad_gge67991.26, Pad_gge67994.26, Pad_gge67997.26, Pad_gge68000.26, Pad_gge68003.26, Pad_gge68006.26, Pad_gge68009.26, Pad_gge68012.26, Pad_gge68015.26, Pad_gge68018.26, Pad_gge68021.26, Pad_gge68024.26, Pad_gge68027.26, Pad_gge68030.10, Pad_gge68033.15, Pad_gge68036.16, Pad_gge68039.22, Pad_gge68042.23, Pad_gge68045.24, Pad_gge68048.25, Pad_gge68051.26, Pad_gge68054.10, Pad_gge68057.15, Pad_gge68060.16, Pad_gge68063.22, Pad_gge68066.23, Pad_gge68069.24, Pad_gge68072.25, Pad_gge68075.26, Pad_gge68078.10, Pad_gge68081.15, Pad_gge68084.16, Pad_gge68087.22, Pad_gge68090.23, Pad_gge68093.24, Pad_gge68096.25, Pad_gge68099.26, Pad_gge68102.10, Pad_gge68105.15, Pad_gge68108.16, Pad_gge68111.22, Pad_gge68114.23, Pad_gge68117.24, Pad_gge68120.25, Pad_gge68123.26, Pad_gge68126.10, Pad_gge68129.15, Pad_gge68132.16, Pad_gge68135.22, Pad_gge68138.23, Pad_gge68141.24, Pad_gge68144.25, Pad_gge68147.26, Pad_gge68150.10, Pad_gge68153.15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
M2-: C16.2, D2.2, J8.2, Pad_gge69722.26, Pad_gge69725.25, Pad_gge69728.24, Pad_gge69731.23, Pad_gge69734.22, Pad_gge69737.16, Pad_gge69740.15, Pad_gge69743.10, Pad_gge69746.26, Pad_gge69749.26, Pad_gge69752.26, Pad_gge69755.25, Pad_gge69758.24, Pad_gge69761.23, Pad_gge69764.22, Pad_gge69767.16, Pad_gge69770.15, Pad_gge69773.10, Pad_gge69776.26, Pad_gge69779.26, Pad_gge69782.26, Pad_gge69785.26, Pad_gge69788.26, Pad_gge69791.26, Pad_gge69794.26, Pad_gge69797.26, Pad_gge69800.26, Pad_gge69803.26, Pad_gge69806.26, Pad_gge69809.26, Pad_gge69812.26, Pad_gge69815.26, Pad_gge69818.26, Pad_gge69821.26, Pad_gge69824.26, Pad_gge69827.26, Pad_gge69830.10, Pad_gge69833.15, Pad_gge69836.16, Pad_gge69839.22, Pad_gge69842.23, Pad_gge69845.24, Pad_gge69848.25, Pad_gge69851.26, Pad_gge69854.10, Pad_gge69857.15, Pad_gge69860.16, Pad_gge69863.22, Pad_gge69866.23, Pad_gge69869.24, Pad_gge69872.25, Pad_gge69875.26, Pad_gge69878.10, Pad_gge69881.15, Pad_gge69884.16, Pad_gge69887.22, Pad_gge69890.23, Pad_gge69893.24, Pad_gge69896.25, Pad_gge69899.26, Pad_gge69902.10, Pad_gge69905.15, Pad_gge69908.16, Pad_gge69911.22, Pad_gge69914.23, Pad_gge69917.24, Pad_gge69920.25, Pad_gge69923.26, Pad_gge69926.10, Pad_gge69929.15, Pad_gge69932.16, Pad_gge69935.22, Pad_gge69938.23, Pad_gge69941.24, Pad_gge69944.25, Pad_gge69947.26, Pad_gge69950.10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
unnamed: C19.1, R32.2
unnamed: C17.1, D3.1, R33.2, U8.3
unnamed: C20.1, D4.1, U9.9
unnamed: D5.2, R36.2
unnamed: C5.1, IC1.34, R26.1
unnamed: C4.1, IC1.35, R25.1
unnamed: C23.2, JP1.1, R38.2, R39.1
unnamed: JP2.1, U10.5
unnamed: J1.2, PM1.4
unnamed: Q1.1, R29.2
unnamed: Q2.1, R30.1
unnamed: R11.2, R17.2, U2.6
unnamed: R12.2, U2.5
unnamed: R13.2, R18.2, U3.6
unnamed: R14.1, U3.5
unnamed: R9.2, R19.2, U4.6
unnamed: R10.2, U4.5
unnamed: R15.1, R20.2, U5.6
unnamed: R16.2, U5.5
unnamed: R21.2, U6.12
unnamed: C18.1, R34.2, R35.1, U9.4
unnamed: R31.1, U9.7
R_IS: C2.2, J6.5, JP5.1, R17.1, R18.1
R_LEN: IC1.12, R4.2, U1.8
R_LPWM: IC1.10, R3.2, U1.6
R_REN: IC1.11, R2.2, U1.4
R_RPWM: IC1.9, R1.2, U1.2
SW: JP3.1, PM1.6
UART1_RX: IC1.17, J4.4
UART1_TX: IC1.16, J4.3
VBAT: H10.2, JP1.2, R26.2
VIN: C9.1, C10.1, C11.1, C12.1, C13.1, C14.1, PM1.1, R37.2, R38.1, U2.7, U3.7, U4.7, U5.7, U10.1
VSW: C19.2, C20.2, Q1.3, Q2.3, R36.1, R37.1, U9.8, U10.8

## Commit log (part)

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2026-03-29 fix: update channel configuration for beacon and ELRS UART connection in documentation
2026-03-30 Revert "fix: switch BTS7960 defaults to hardware PWM wiring"
    This reverts commit 6bb448f5e804b4104f4902527d2564727451e784.
2026-03-30 feat: add two-channel motor melody polyphony
2026-03-30 fix: reduce roll during motor melodies
2026-03-30 Wait for ADS1115 conversions
2026-03-31 test: pin MotorSynth hardware mode in wav tests
2026-03-31 feat: redesign biba synth voice
2026-03-31 feat: add numeric motor test frequency inputs
2026-04-01 fix: update PWM settings for motor control in MotorSynth
2026-04-01 fix: allow freeform manual frequency input
2026-04-01 test: fix trim expectations for 30 percent max effect
2026-04-01 feat: add Lua speed mode selector
2026-04-02 chore: sync docs and operator scripts
2026-04-06 Add IMU-assisted drive modes
2026-04-06 fix: preserve steering intent in assisted modes
2026-04-06 fix: tame assisted-drive steering oscillation
2026-04-08 feat: add persisted pid tuning page
2026-04-22 feat(fw+sbc): add stm32 firmware HAL/modes scaffolding and Python stm32_link
    Agent-Logs-Url: https://github.com/GOODWORKRINKZ/biba/sessions/5eeced37-6c6b-4464-a634-e94bfde884ec
2026-04-22 refactor: move firmware/stm32f103/* to firmware/* (stm32f103 is just a target/MCU, not the project scope)
    Agent-Logs-Url: https://github.com/GOODWORKRINKZ/biba/sessions/b0bcbf08-2660-4daf-8140-9faba8125617
2026-04-27 feat: add ARM semihosting printf redirect for debugging support
2026-04-28 docs(plan): add docs refactor and compose relocation implementation plan
2026-04-28 chore(scripts): route update.sh and diagnostics.sh through BIBA_COMPOSE_FILE
2026-04-28 docs(stm32): cross-link to system_architecture.md and label modes by composition
2026-04-28 feat(docker): add ROS2 base images and CI workflow
    - docker/base/Dockerfile.ros2-zenoh: ROS 2 Humble + rmw_zenoh_cpp + colcon
    - docker/base/Dockerfile.ros2-control: extends zenoh with ros2_control,
    diff_drive_controller, twist_mux, robot_state_publisher, xacro
    - .github/workflows/G-Build-ROS2-Bases.yml: builds both as linux/arm64,
    pushes to ghcr.io/<repo>/biba-ros2-zenoh and biba-ros2-control,
    reuses tag scheme from controller image workflow
2026-04-28 feat(biba_bringup): add twist_mux config + launch + compose service
    Composition C arbitrates SBC-side cmd_vel sources via twist_mux.
    CRSF stays on STM32 (independent failsafe), so the mux only ranks
    operator/uwb/autonomy inputs and routes the winner to /cmd_vel,
    which biba_stm32_bridge consumes.
    - config/twist_mux.yaml: teleop > uwb_follow > autonomy, /biba/estop lock
    - launch/twist_mux.launch.py: loads share config, remaps cmd_vel_out -> /cmd_vel
2026-04-28 fix(ci): satisfy shellcheck and lowercase GHCR image refs
    - setup_node_ros2.sh: silence SC2294 (intentional eval of shell-string
    arg) and replace 'echo | sed' (SC2001) with bash parameter expansion
    - workflows: hardcode lowercase 'goodworkrinkz/biba' in image env vars
    instead of ${{ github.repository }} (which preserves the original
    org casing); Docker reference parser rejects mixed-case repo names
    on FROM/--tag, breaking the biba-ros2-control build
2026-05-07 feat(rp2040): update target.h and add target.md for RPICO_RP2040 pinout and configuration details
2026-05-08 feat(rp2040): add SOS beacon melody and integrate into standalone mode
2026-05-14 chore: add codebase map (.planning/codebase/)
    7 documents generated by gsd-map-codebase on 2026-05-14:
    - STACK.md (151 lines) - tech stack, deps, config
    - INTEGRATIONS.md (180 lines) - hardware interfaces, protocols
    - ARCHITECTURE.md (207 lines) - patterns, layers, data flow
    - STRUCTURE.md (249 lines) - directory layout, module map
    - CONVENTIONS.md (179 lines) - code style, patterns
2026-05-14 docs: create roadmap (3 phases)
2026-05-14 feat(01-01): create ramp.h struct/declarations and biba_config.h RAMP constants
2026-05-14 feat(01-03): add Unity test suite for biba_ramp — 8 tests GREEN; fix native_test build filter (main_rp2040.cpp, melody.c) and BIBA_NATIVE_TEST guard in biba_config.h
2026-05-14 docs(01-05): hardware verify PASSED — Phase 1 complete, 2 backlog findings captured
2026-05-16 feat: add reverse backup pip functionality with configurable interval
2026-05-17 docs(thermal): integrate industry references into design spec — Rds_on formula, synchronous rectification, dead time, capacitor design
    - Add conduction loss formula: P_loss = I² × Rds_on
    - Compare BTN8982TA (9W @ 30A) vs BTS7960 (14.4W) — 35% reduction
    - Validate MOSFET choice for 24V via Arduino forum community consensus (<200V rule)
    - Document synchronous rectification (Cytron Design) replaces diode losses
    - Detail dead time protection (A3941 IC prevents shoot-through)
    - Explain main capacitor role in voltage stabilization and thermal performance
2026-05-19 plan(05): add phase 05 PLAN.md — ADS1115/AHT30/IBAT/telemetry
2026-05-19 docs(05): add 05-SUMMARY.md for current sensing ADC phase
2026-05-22 docs(06): capture phase context
2026-05-22 feat(06-task2): add rpico_rp2040_is_poc PlatformIO env
2026-05-22 test(06-task7): unit tests FFT/ZC/autocorr ±5%, add numpy/scipy to requirements-dev.txt
2026-05-22 fix(rp2040): also disable per-motor power limiter (uses same IS sample)
2026-05-22 feat(06): closed-loop PI controller for IS-PoC
    Firmware: new RPMRUN <target_hz> <duration_ms> [kp_x1000 ki_x1000] command
    in is_rpm_poc_main.cpp.
    Pipeline per 200 ms iteration (5 Hz loop rate):
    1. Capture 2048 samples @ 10 kSPS from IS_LEFT (DMA burst)
    2. On-device Schmitt-trigger zero-crossing → measured_hz
    (hysteresis = 0.25 × peak-to-peak, robust against ADC noise)
2026-05-22 Add IS signal PoC scripts for RPM and step response testing
    - Introduced `is_poc_pid.py` for open-loop RPM control with enhanced PID parameters and error handling.
    - Added `is_poc_step.py` for open-loop step response testing, capturing frequency response and plotting results.
    - Created CSV output files for both RPM and step tests to log measurements.
    - Generated PNG plots for visualizing RPM and step response data.
    - Updated argument parsing to include new parameters for stiction and feed-forward control in PID testing.
2026-05-23 feat: add step response analysis images for IS signal testing
2026-05-23 docs(07): create phase 07 IS-RPM integration plans (5 plans, 3 waves)
    Wave 1 (parallel):
    - 07-01: zc_detector.h/c + adc_capture async + test_zc_detector
    - 07-02: biba_proto extension + Python decoder + speed estimation + tests
    - 07-03: CALRUN command + is_rpm_calibrate.py script
    Wave 2 (depends 07-01):
    - 07-04: rpm_pi.h/c + test_rpm_pi
2026-05-23 test(07-01): add test_zc_detector (5 Unity tests, all pass) + fix native_test build (poc exclusion, libm link)
2026-05-23 feat(07-03): add CALRUN command to PoC firmware
    CALRUN <duty_pct> <settle_ms>: drives IS_LEFT at duty_pct% forward,
    settles, then captures 1024@10kSPS five times. Median ZC freq is
    reported as 'IS_HZ <duty_pct> <hz_x100>' (0.01 Hz resolution). Motor
    is always stopped before returning. Args validated: duty 0..100,
    settle_ms 100..10000 -> 'ERROR bad args' on out-of-range.
2026-05-23 docs(07-04): plan summary
2026-05-23 refactor: simplify drive input handling and remove envelope limiter for improved steering authority
2026-05-24 feat(scripts): add sweepraw analysis tools and capture artifacts
    - is_poc_sweepraw.py: updated for SWEEPRAW_BOTH command support
    - is_poc_capture.py: updated for CAPTURE_R command
    - is_poc_raw_analyze.py: new script to analyze pkpk/ZC per sweepraw window
    - is_biba_drive_capture.py: new script to capture DRIVE_DATA telemetry
    - artifacts/is-sweepraw/: 4 sweepraw datasets (LEFT_only, RIGHT_only, BOTH×2)
    used to calibrate ZC_SUBWIN_MIN_PKPK threshold
2026-05-24 Add window algorithm evaluation summary image to artifacts
2026-05-25 fix(rpm_pi): enhance stall recovery and adjust anti-windup logic
2026-05-25 refactor(voltage_sense): replace ADS1115 reads with HAL ADC functions for voltage sensing
2026-05-25 Add new scripts for dual-wheel closed-loop capture and analysis
    - Introduced `is_poc_both_hold.py` for capturing telemetry from the RP2040 firmware with manual hold intervals.
    - Added `is_sweepraw_analyze.py` enhancements to include a Python port of the Goertzel spectral estimator for improved analysis of SWEEPRAW captures.
    - Included multiple new PNG artifacts for visual representation of the data.
    - Updated plotting functionality to visualize spectral output and quality metrics alongside duty commands and ZC algorithm estimates.
2026-05-25 docs(phase-8): create phase plans 01-03
    - 08-01: LittleFS wrapper foundation (blackbox.h/cpp, config, hal serial, native tests)
    - 08-02: mode_standalone.c BB state machine (CH8, arm/disarm, per-tick record, flash-full)
    - 08-03: CDC bb shell commands + biba_blackbox_download.py
    - ROADMAP.md updated with 3 plans across 3 waves
2026-05-26 spec(phase-09): RPM dead-reckoning fallback — 7 requirements, simulation gate before firmware
2026-05-26 plan(phase-09): 3-wave plan — Python sim gate + firmware DR module + integration tests
2026-05-26 spec(phase-10): Goertzel dual-window search — hint_hz extends plant-model search
    Root cause (session analysis): plant model error at low duty (28%) places
    search band 128-288 Hz while actual IS peak is at ~370 Hz (amp=52, above
    threshold). Second window centred on previous valid freq_hz reduces FWD
    dropout 22% → 15% on amp100/per8000 fullsine sweep.
    Decisions locked in SPEC:
    - Extend existing biba_rpm_spectral_estimate() signature with hint_hz param
2026-05-26 research(phase-10): dual-window research script + spectral_estimate_hint()
    - Add spectral_estimate_hint(buf, sps, target_hz, hint_hz=0.0) to
    is_sweepraw_analyze.py as additive extension; sentinel hint_hz=0.0
    returns identical result to spectral_estimate() (backward-compat)
    - Create scripts/is_hint_research.py: batch simulation over all 28
    sweepraw CSV files; both hint_reset_on_dir variants on TRAP files
    - Research findings: pooled +1.6pp improvement (gate: >=1pp PASS);
2026-05-26 docs(phase-11): research — load gate API, SWEEPRAW extension, threshold verification
2026-05-26 feat(phase-11): 4-channel round-robin DMA — IS_L+IS_R+VBAT+IBAT in one burst
    Added adc_capture_init_4ch() and adc_capture_burst_4ch() to app/adc_capture.c.
    cmd_sweepraw_both() now captures all 4 channels simultaneously in round-robin
    DMA mode (GP26=IS_L, GP27=IS_R, GP28=VBAT, GP29=IBAT).
    VBAT/IBAT are now per-window DC means (1024 samples each), printed in the
    SWEEPRAW2_WIN L header line. Python parser extracts per-window values.
    VBAT calibration: BIBA_VBAT_DIVIDER_RATIO=10.12 (verified against 23.3V multimeter)
2026-05-27 plan(phase-12): 3-wave plan — config reorganization + mode_standalone.c gates + build verification + smoke test
